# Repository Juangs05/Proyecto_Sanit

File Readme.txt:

Archivo de prueba para el montaje del proyecto de Santi para el curso de dispositivos médicos wearable

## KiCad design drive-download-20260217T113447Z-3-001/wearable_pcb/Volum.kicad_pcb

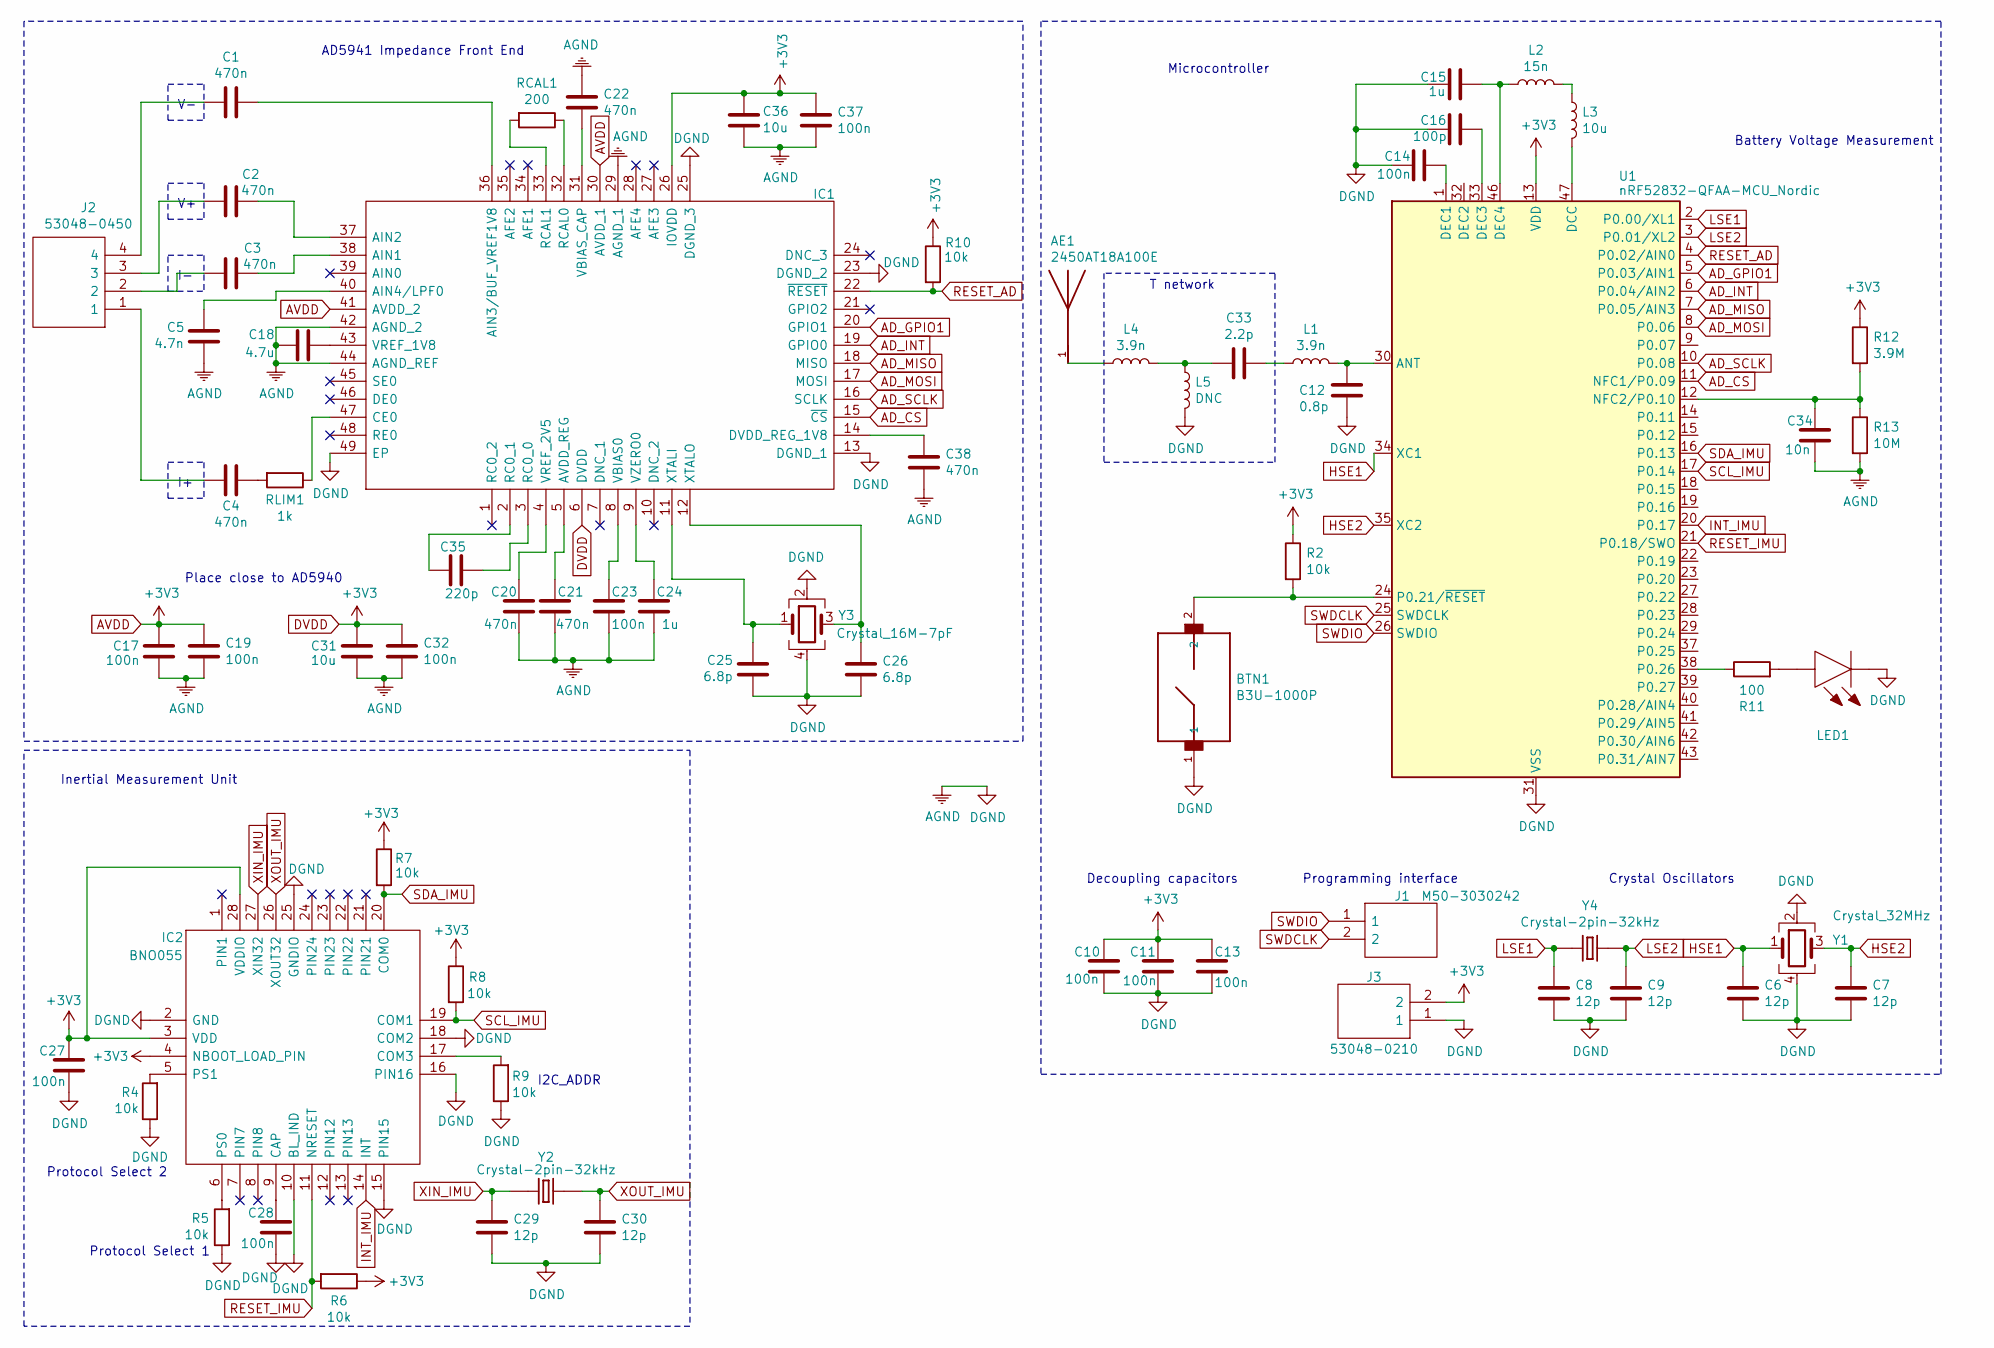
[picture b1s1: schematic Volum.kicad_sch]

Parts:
AE1: 2450AT18A100E; ANTC3216X140N
BTN1: B3U-1000P; SW_B3U-1000P
C1, C2, C3, C4, C20, C21, C22, C38: 470n; C_0402
C5: 4.7n; C_0402
C6, C7, C8, C9, C29, C30: 12p; C_0402
C10, C11, C13, C14, C17, C19, C23, C27, C28, C32, C37: 100n; C_0402
C12: 0.8p; C_0402
C15, C24: 1u; C_0402
C16: 100p; C_0402
C18: 4.7u; C_0402
C25, C26: 6.8p; C_0402
C31, C36: 10u; C_0402
C33: 2.2p; C_0402
C34: 10n; C_0402
C35: 220p; C_0402
IC1: AD5941BCPZ; QFN50P700X700X80-49N-D; Manufacturer_Part_Number AD5941BCPZ
IC2: BNO055; Manufacturer_Part_Number BNO055
J1: M50-3030242; M503030242; Manufacturer_Part_Number M50-3030242
J2: 53048-0450; Molex_PicoBlade_53048-0450; Manufacturer_Part_Number 53048-0450; Mouser Part Number 538-53048-0450
J3: 53048-0210; SHDRRA2W35P0X125_1X2_425X550X350P; Manufacturer_Part_Number 53048-0210
L1, L4: 3.9n; L_0402
L2: 15n; L_0402
L3: 10u; L_0402
L5: DNC; L_0402
LED1: LEDGr_VCDG1113F-4BY3C-TR; VCDG1113F4BY3CTR; Manufacturer_Part_Number VCDG1113F-4BY3C-TR; Mouser Part Number 327-VCDG1113F4BY3CTR
R2, R4, R5, R6, R7, R8, R9, R10: 10k; R_0402
R11: 100; R_0402
R12: 3.9M; R_0402
R13: 10M; R_0402
RCAL1: 200; R_0402
RLIM1: 1k; R_0402
U1: nRF52832-QFAA-MCU_Nordic; QFN-48-1EP_6x6mm_Pitch0.4mm
Y1: Crystal_32MHz; ECS320833B7KMTR
Y2, Y4: Crystal-2pin-32kHz; ECS32712512RCTR
Y3: Crystal_16M-7pF; ABM810000MHZ12D2W

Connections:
AD_CS: IC1.15 (~CS), U1.11 (NFC1/P0.09)
AD_GPIO1: IC1.20 (GPIO1), U1.5 (P0.03/AIN1)
AD_INT: IC1.19 (GPIO0), U1.6 (P0.04/AIN2)
AD_MISO: IC1.18 (MISO), U1.7 (P0.05/AIN3)
AD_MOSI: IC1.17 (MOSI), U1.8 (P0.06)
AD_SCLK: IC1.16 (SCLK), U1.10 (P0.08)
AGND: BTN1.1, C5.2, C6.2, C7.2, C8.2, C9.2, C10.2, C11.2, C12.2, C13.2, C14.2, C15.2, C16.2, C17.2, C18.2, C19.2, C20.2, C21.2, C22.1, C23.2, C24.2, C25.2, C26.2, C27.2, C28.2, C29.2, C30.2, C31.2, C32.2, C34.2, C36.2, C37.2, C38.2, IC1.13 (DGND_1), IC1.23 (DGND_2), IC1.25 (DGND_3), IC1.29 (AGND_1), IC1.42 (AGND_2), IC1.44 (AGND_REF), IC1.49 (EP), IC2.2 (GND), IC2.10 (BL_IND), IC2.15 (PIN15), IC2.16 (PIN16), IC2.18 (COM2), IC2.25 (GNDIO), J3.1, L5.2, LED1.1 (K), R4.1, R5.1, R9.1, R13.2, U1.31 (VSS), U1.45 (VSS), U1.49 (VSS), Y1.2, Y1.4, Y3.2, Y3.4
AVDD: C10.1, C11.1, C13.1, C17.1, C19.1, C27.1, C31.1, C32.1, C36.1, C37.1, IC1.6 (DVDD), IC1.26 (IOVDD), IC1.30 (AVDD_1), IC1.41 (AVDD_2), IC2.3 (VDD), IC2.4 (NBOOT_LOAD_PIN), IC2.28 (VDDIO), J3.2, R2.1, R6.1, R7.1, R8.1, R10.1, R12.1, U1.13 (VDD), U1.36 (VDD), U1.48 (VDD)
HSE1: C6.1, U1.34 (XC1), Y1.1
HSE2: C7.1, U1.35 (XC2), Y1.3
INT_IMU: IC2.14 (INT), U1.20 (P0.17)
LSE1: C8.1, U1.2 (P0.00/XL1), Y4.1
LSE2: C9.1, U1.3 (P0.01/XL2), Y4.2
unnamed: AE1.1, L4.1
unnamed: C1.2, J2.4
unnamed: C2.2, J2.3
unnamed: C3.2, J2.2
unnamed: C4.1, RLIM1.2
unnamed: C4.2, J2.1
unnamed: C33.1, L1.1
unnamed: C33.2, L4.2, L5.1
unnamed: C3.1, IC1.38 (AIN1)
unnamed: C2.1, IC1.37 (AIN2)
unnamed: C1.1, IC1.36 (AIN3/BUF_VREF1V8)
unnamed: C5.1, IC1.40 (AIN4/LPF0)
unnamed: C21.1, IC1.5 (AVDD_REG)
unnamed: IC1.47 (CE0), RLIM1.1
unnamed: C38.1, IC1.14 (DVDD_REG_1V8)
unnamed: C35.2, IC1.3 (RC0_0)
unnamed: C35.1, IC1.2 (RC0_1)
unnamed: IC1.32 (RCAL0), RCAL1.1
unnamed: IC1.33 (RCAL1), RCAL1.2
unnamed: C23.1, IC1.8 (VBIAS0)
unnamed: C22.2, IC1.31 (VBIAS_CAP)
unnamed: C18.1, IC1.43 (VREF_1V8)
unnamed: C20.1, IC1.4 (VREF_2V5)
unnamed: C24.1, IC1.9 (VZERO0)
unnamed: C25.1, IC1.11 (XTALI), Y3.1
unnamed: C26.1, IC1.12 (XTALO), Y3.3
unnamed: C28.1, IC2.9 (CAP)
unnamed: IC2.17 (COM3), R9.2
unnamed: IC2.6 (PS0), R5.2
unnamed: IC2.5 (PS1), R4.2
unnamed: L2.2, L3.1
unnamed: LED1.2 (A), R11.2
unnamed: C12.1, L1.2, U1.30 (ANT)
unnamed: L3.2, U1.47 (DCC)
unnamed: C14.1, U1.1 (DEC1)
unnamed: C16.1, U1.33 (DEC3)
unnamed: C15.1, L2.1, U1.46 (DEC4)
unnamed: C34.1, R12.2, R13.1, U1.12 (NFC2/P0.10)
unnamed: BTN1.2, R2.2, U1.24 (P0.21/~RESET)
unnamed: R11.1, U1.38 (P0.26)
RESET_AD: IC1.22 (~RESET), R10.2, U1.4 (P0.02/AIN0)
RESET_IMU: IC2.11 (NRESET), R6.2, U1.21 (P0.18/SWO)
SCL_IMU: IC2.19 (COM1), R8.2, U1.17 (P0.14)
SDA_IMU: IC2.20 (COM0), R7.2, U1.16 (P0.13)
SWDCLK: J1.2, U1.25 (SWDCLK)
SWDIO: J1.1, U1.26 (SWDIO)
XIN_IMU: C29.1, IC2.27 (XIN32), Y2.1
XOUT_IMU: C30.1, IC2.26 (XOUT32), Y2.2

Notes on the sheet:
AD5941 Impedance Front End
Inertial Measurement Unit
T network
Programming interface
Decoupling capacitors
Battery Voltage Measurement
Crystal Oscillators
I2C_ADDR
Microcontroller
Protocol Select 1
Place close to AD5940
Protocol Select 2

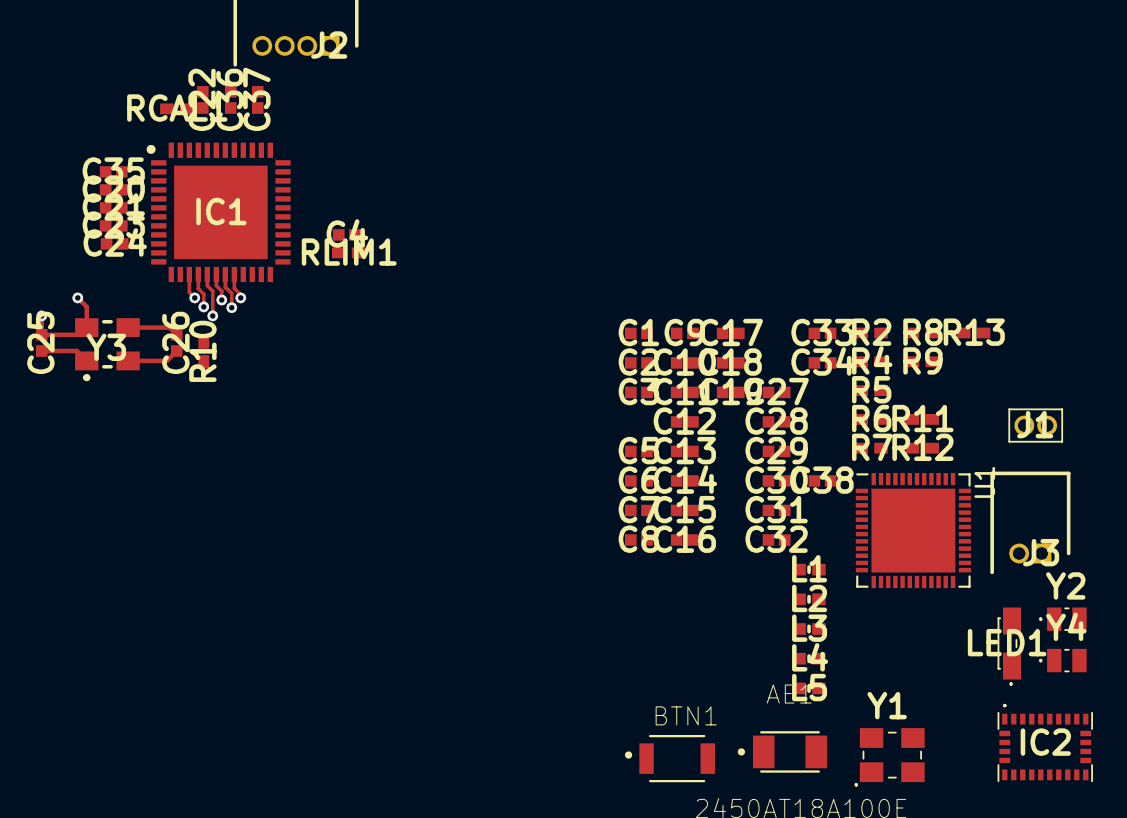
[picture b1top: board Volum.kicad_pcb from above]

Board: 4 copper layers, 69 parts (0 on the bottom side), 61 nets.
